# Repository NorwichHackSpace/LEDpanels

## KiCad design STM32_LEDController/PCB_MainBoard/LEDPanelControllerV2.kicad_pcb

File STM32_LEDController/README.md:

# STM32 LED Panel Controller
This controller is centered around an STM32L031C6T which can control up to 8 panels using its GPIOB output register to set 16 data lines at once, currently the code only uses 4 of the panel outputs. The output is buffered through some 74LVC2G17GW Schmitt triggers which can output at 3.3V or 5V. The main board also includes space for an optional RFM69W 433MHz module.

The main board is powered by an ATX 24-pin connector, the STM32 chip is powered by the 5V standby line (dropped to 3.3V by an LDO) whist the output buffers are powered by either the 3.3V line or the main 5V line. The STM32 controls the PSU power pin and can turn the rest of the PSU on or off whilst being powered by the standby line.

The remaining GPIO pins are broken out onto a pin header, along with GND, 3.3V (standby), and the reset pin. A HAT has been included that can provide up to 8 button inputs, assuming the 433MHz module is not present. The buttons should just connect the signal line directly to ground when pressed.

The code was compiled using STM32CubeIDE and can be uploaded by using a cheap ST-Link V2 programmer from ebay.

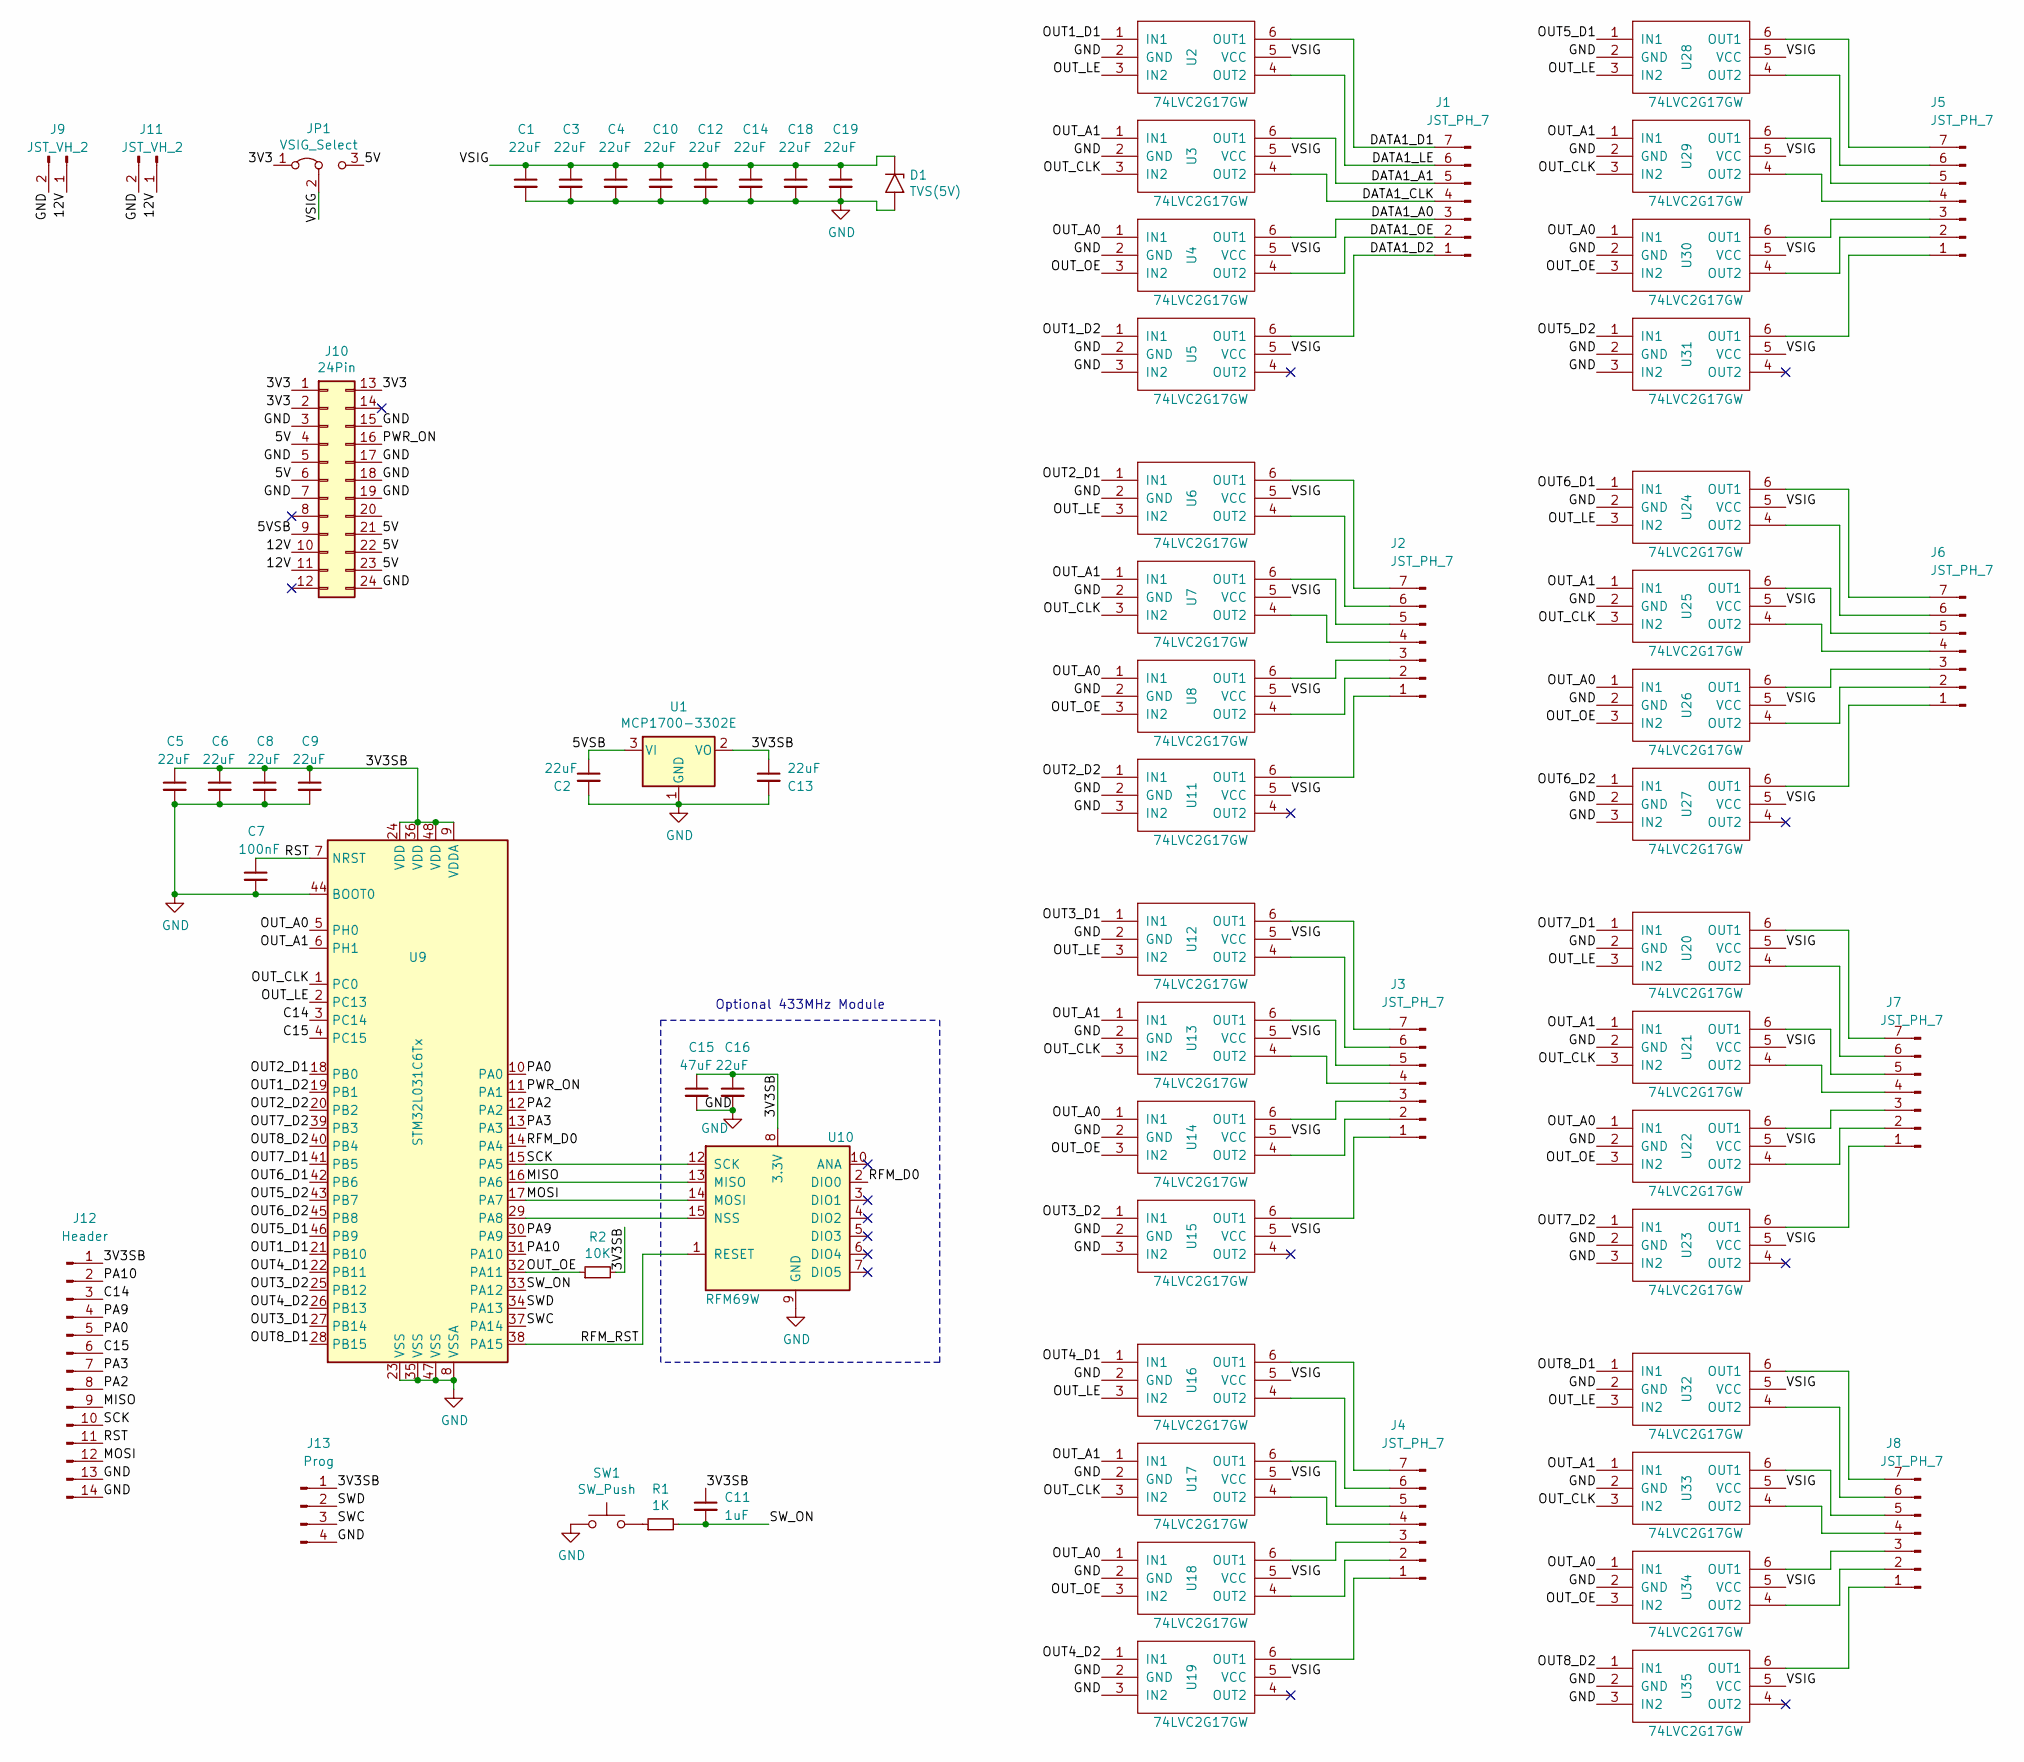
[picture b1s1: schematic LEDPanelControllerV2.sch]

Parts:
C1, C2, C3, C4, C5, C6, C8, C9, C10, C12, C13, C14, C16, C18, C19: 22uF; R_0603_HandSoldering2
C7: 100nF; R_0603_HandSoldering2
C11: 1uF; R_0603_HandSoldering2
C15: 47uF; R_1206_HandSoldering
D1: TVS(5V); DO_214AC
J1, J2, J3, J4, J5, J6, J7, J8: JST_PH_7; JST_PH_S7B-PH-SM4-TB_07x2.00mm_Angled
J9, J11: JST_VH_2; JST_VH_B2P-VH-B_2x3.96mm_Vertical
J10: 24Pin; Molex_MiniFit-JR-5569-24A2_2x12x4.20mm_Angled
J12: Header; Pin_Header_Straight_2x07_Pitch2.54mm
J13: Prog; Pin_Header_Straight_2x02_Pitch2.54mm
JP1: VSIG_Select; Pin_Header_Straight_1x03_Pitch2.54mm
R1: 1K; R_0603_HandSoldering2
R2: 10K; R_0603_HandSoldering2
SW1: SW_Push; SW_SPST_EVQQ2
U1: MCP1700-3302E; SOT-23
U2, U3, U4, U5, U6, U7, U8, U11, U12, U13, U14, U15, U16, U17, U18, U19, U20, U21, U22, U23, U24, U25, U26, U27, U28, U29, U30, U31, U32, U33, U34, U35: 74LVC2G17GW; SOT-363_SC-70-6
U9: STM32L031C6Tx; LQFP-48_7x7mm_Pitch0.5mm
U10: RFM69W; RFM69

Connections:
/3V3: J10.1, J10.2, J10.13, JP1.1 (A)
/3V3SB: C5.1, C6.1, C8.1, C9.1, C11.1, C13.1, C15.1, C16.1, J12.1, J13.1, R2.2, U1.2 (VO), U9.9 (VDDA), U9.24 (VDD), U9.36 (VDD), U9.48 (VDD), U10.8 (3.3V)
/5V: J10.4, J10.6, J10.21, J10.22, J10.23, JP1.3 (B)
/5VSB: C2.1, J10.9, U1.3 (VI)
/12V: J9.1, J10.10, J10.11, J11.1
/C14: J12.3, U9.3 (PC14)
/C15: J12.6, U9.4 (PC15)
/DATA1_A0: J1.3, U4.6 (OUT1)
/DATA1_A1: J1.5, U3.6 (OUT1)
/DATA1_CLK: J1.4, U3.4 (OUT2)
/DATA1_D1: J1.7, U2.6 (OUT1)
/DATA1_D2: J1.1, U5.6 (OUT1)
/DATA1_LE: J1.6, U2.4 (OUT2)
/DATA1_OE: J1.2, U4.4 (OUT2)
/MISO: J12.9, U9.16 (PA6), U10.13 (MISO)
/MOSI: J12.12, U9.17 (PA7), U10.14 (MOSI)
/OUT1_D1: U2.1 (IN1), U9.21 (PB10)
/OUT1_D2: U5.1 (IN1), U9.19 (PB1)
/OUT2_D1: U6.1 (IN1), U9.18 (PB0)
/OUT2_D2: U9.20 (PB2), U11.1 (IN1)
/OUT3_D1: U9.27 (PB14), U12.1 (IN1)
/OUT3_D2: U9.25 (PB12), U15.1 (IN1)
/OUT4_D1: U9.22 (PB11), U16.1 (IN1)
/OUT4_D2: U9.26 (PB13), U19.1 (IN1)
/OUT5_D1: U9.46 (PB9), U28.1 (IN1)
/OUT5_D2: U9.43 (PB7), U31.1 (IN1)
/OUT6_D1: U9.42 (PB6), U24.1 (IN1)
/OUT6_D2: U9.45 (PB8), U27.1 (IN1)
/OUT7_D1: U9.41 (PB5), U20.1 (IN1)
/OUT7_D2: U9.39 (PB3), U23.1 (IN1)
/OUT8_D1: U9.28 (PB15), U32.1 (IN1)
/OUT8_D2: U9.40 (PB4), U35.1 (IN1)
/OUT_A0: U4.1 (IN1), U8.1 (IN1), U9.5 (PH0), U14.1 (IN1), U18.1 (IN1), U22.1 (IN1), U26.1 (IN1), U30.1 (IN1), U34.1 (IN1)
/OUT_A1: U3.1 (IN1), U7.1 (IN1), U9.6 (PH1), U13.1 (IN1), U17.1 (IN1), U21.1 (IN1), U25.1 (IN1), U29.1 (IN1), U33.1 (IN1)
/OUT_CLK: U3.3 (IN2), U7.3 (IN2), U9.1 (PC0), U13.3 (IN2), U17.3 (IN2), U21.3 (IN2), U25.3 (IN2), U29.3 (IN2), U33.3 (IN2)
/OUT_LE: U2.3 (IN2), U6.3 (IN2), U9.2 (PC13), U12.3 (IN2), U16.3 (IN2), U20.3 (IN2), U24.3 (IN2), U28.3 (IN2), U32.3 (IN2)
/OUT_OE: R2.1, U4.3 (IN2), U8.3 (IN2), U9.32 (PA11), U14.3 (IN2), U18.3 (IN2), U22.3 (IN2), U26.3 (IN2), U30.3 (IN2), U34.3 (IN2)
/PA0: J12.5, U9.10 (PA0)
/PA2: J12.8, U9.12 (PA2)
/PA3: J12.7, U9.13 (PA3)
/PA9: J12.4, U9.30 (PA9)
/PA10: J12.2, U9.31 (PA10)
/PWR_ON: J10.16, U9.11 (PA1)
/RFM_D0: U9.14 (PA4), U10.2 (DIO0)
/RFM_RST: U9.38 (PA15), U10.1 (RESET)
/RST: C7.1, J12.11, U9.7 (NRST)
/SCK: J12.10, U9.15 (PA5), U10.12 (SCK)
/SWC: J13.3, U9.37 (PA14)
/SWD: J13.2, U9.34 (PA13)
/SW_ON: C11.2, R1.2, U9.33 (PA12)
/VSIG: C1.1, C3.1, C4.1, C10.1, C12.1, C14.1, C18.1, C19.1, D1.1 (A1), JP1.2 (C), U2.5 (VCC), U3.5 (VCC), U4.5 (VCC), U5.5 (VCC), U6.5 (VCC), U7.5 (VCC), U8.5 (VCC), U11.5 (VCC), U12.5 (VCC), U13.5 (VCC), U14.5 (VCC), U15.5 (VCC), U16.5 (VCC), U17.5 (VCC), U18.5 (VCC), U19.5 (VCC), U20.5 (VCC), U21.5 (VCC), U22.5 (VCC), U23.5 (VCC), U24.5 (VCC), U25.5 (VCC), U26.5 (VCC), U27.5 (VCC), U28.5 (VCC), U29.5 (VCC), U30.5 (VCC), U31.5 (VCC), U32.5 (VCC), U33.5 (VCC), U34.5 (VCC), U35.5 (VCC)
GND: C1.2, C2.2, C3.2, C4.2, C5.2, C6.2, C7.2, C8.2, C9.2, C10.2, C12.2, C13.2, C14.2, C15.2, C16.2, C18.2, C19.2, D1.2 (A2), J9.2, J10.3, J10.5, J10.7, J10.15, J10.17, J10.18, J10.19, J10.24, J11.2, J12.13, J12.14, J13.4, SW1.1, U1.1 (GND), U2.2 (GND), U3.2 (GND), U4.2 (GND), U5.2 (GND), U5.3 (IN2), U6.2 (GND), U7.2 (GND), U8.2 (GND), U9.8 (VSSA), U9.23 (VSS), U9.35 (VSS), U9.44 (BOOT0), U9.47 (VSS), U10.9 (GND), U10.11 (GND), U11.2 (GND), U11.3 (IN2), U12.2 (GND), U13.2 (GND), U14.2 (GND), U15.2 (GND), U15.3 (IN2), U16.2 (GND), U17.2 (GND), U18.2 (GND), U19.2 (GND), U19.3 (IN2), U20.2 (GND), U21.2 (GND), U22.2 (GND), U23.2 (GND), U23.3 (IN2), U24.2 (GND), U25.2 (GND), U26.2 (GND), U27.2 (GND), U27.3 (IN2), U28.2 (GND), U29.2 (GND), U30.2 (GND), U31.2 (GND), U31.3 (IN2), U32.2 (GND), U33.2 (GND), U34.2 (GND), U35.2 (GND), U35.3 (IN2)
unnamed: J2.1, U11.6 (OUT1)
unnamed: J2.2, U8.4 (OUT2)
unnamed: J2.3, U8.6 (OUT1)
unnamed: J2.4, U7.4 (OUT2)
unnamed: J2.5, U7.6 (OUT1)
unnamed: J2.6, U6.4 (OUT2)
unnamed: J2.7, U6.6 (OUT1)
unnamed: J3.1, U15.6 (OUT1)
unnamed: J3.2, U14.4 (OUT2)
unnamed: J3.3, U14.6 (OUT1)
unnamed: J3.4, U13.4 (OUT2)
unnamed: J3.5, U13.6 (OUT1)
unnamed: J3.6, U12.4 (OUT2)
unnamed: J3.7, U12.6 (OUT1)
unnamed: J4.1, U19.6 (OUT1)
unnamed: J4.2, U18.4 (OUT2)
unnamed: J4.3, U18.6 (OUT1)
unnamed: J4.4, U17.4 (OUT2)
unnamed: J4.5, U17.6 (OUT1)
unnamed: J4.6, U16.4 (OUT2)
unnamed: J4.7, U16.6 (OUT1)
unnamed: J5.1, U31.6 (OUT1)
unnamed: J5.2, U30.4 (OUT2)
unnamed: J5.3, U30.6 (OUT1)
unnamed: J5.4, U29.4 (OUT2)
unnamed: J5.5, U29.6 (OUT1)
unnamed: J5.6, U28.4 (OUT2)
unnamed: J5.7, U28.6 (OUT1)
unnamed: J6.1, U27.6 (OUT1)
unnamed: J6.2, U26.4 (OUT2)
unnamed: J6.3, U26.6 (OUT1)
unnamed: J6.4, U25.4 (OUT2)
unnamed: J6.5, U25.6 (OUT1)
unnamed: J6.6, U24.4 (OUT2)
unnamed: J6.7, U24.6 (OUT1)
unnamed: J7.1, U23.6 (OUT1)
unnamed: J7.2, U22.4 (OUT2)
unnamed: J7.3, U22.6 (OUT1)
unnamed: J7.4, U21.4 (OUT2)
unnamed: J7.5, U21.6 (OUT1)
unnamed: J7.6, U20.4 (OUT2)
unnamed: J7.7, U20.6 (OUT1)
unnamed: J8.1, U35.6 (OUT1)
unnamed: J8.2, U34.4 (OUT2)
unnamed: J8.3, U34.6 (OUT1)
unnamed: J8.4, U33.4 (OUT2)
unnamed: J8.5, U33.6 (OUT1)
unnamed: J8.6, U32.4 (OUT2)
unnamed: J8.7, U32.6 (OUT1)
unnamed: R1.1, SW1.2
unnamed: U9.29 (PA8), U10.15 (NSS)

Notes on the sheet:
Optional 433MHz Module

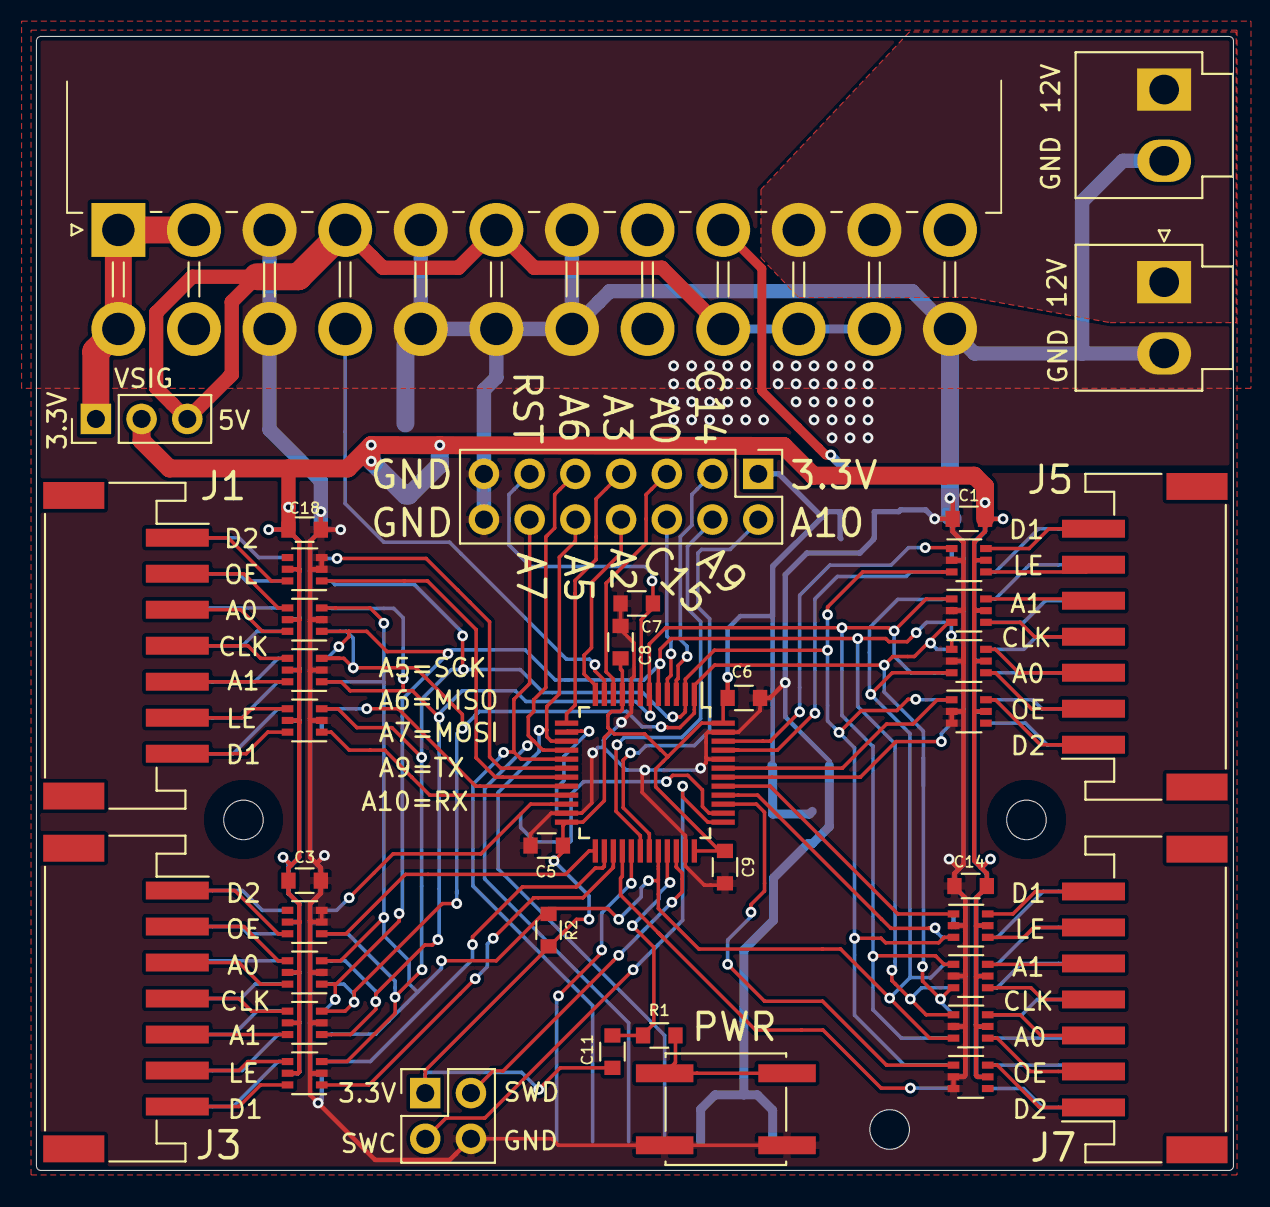
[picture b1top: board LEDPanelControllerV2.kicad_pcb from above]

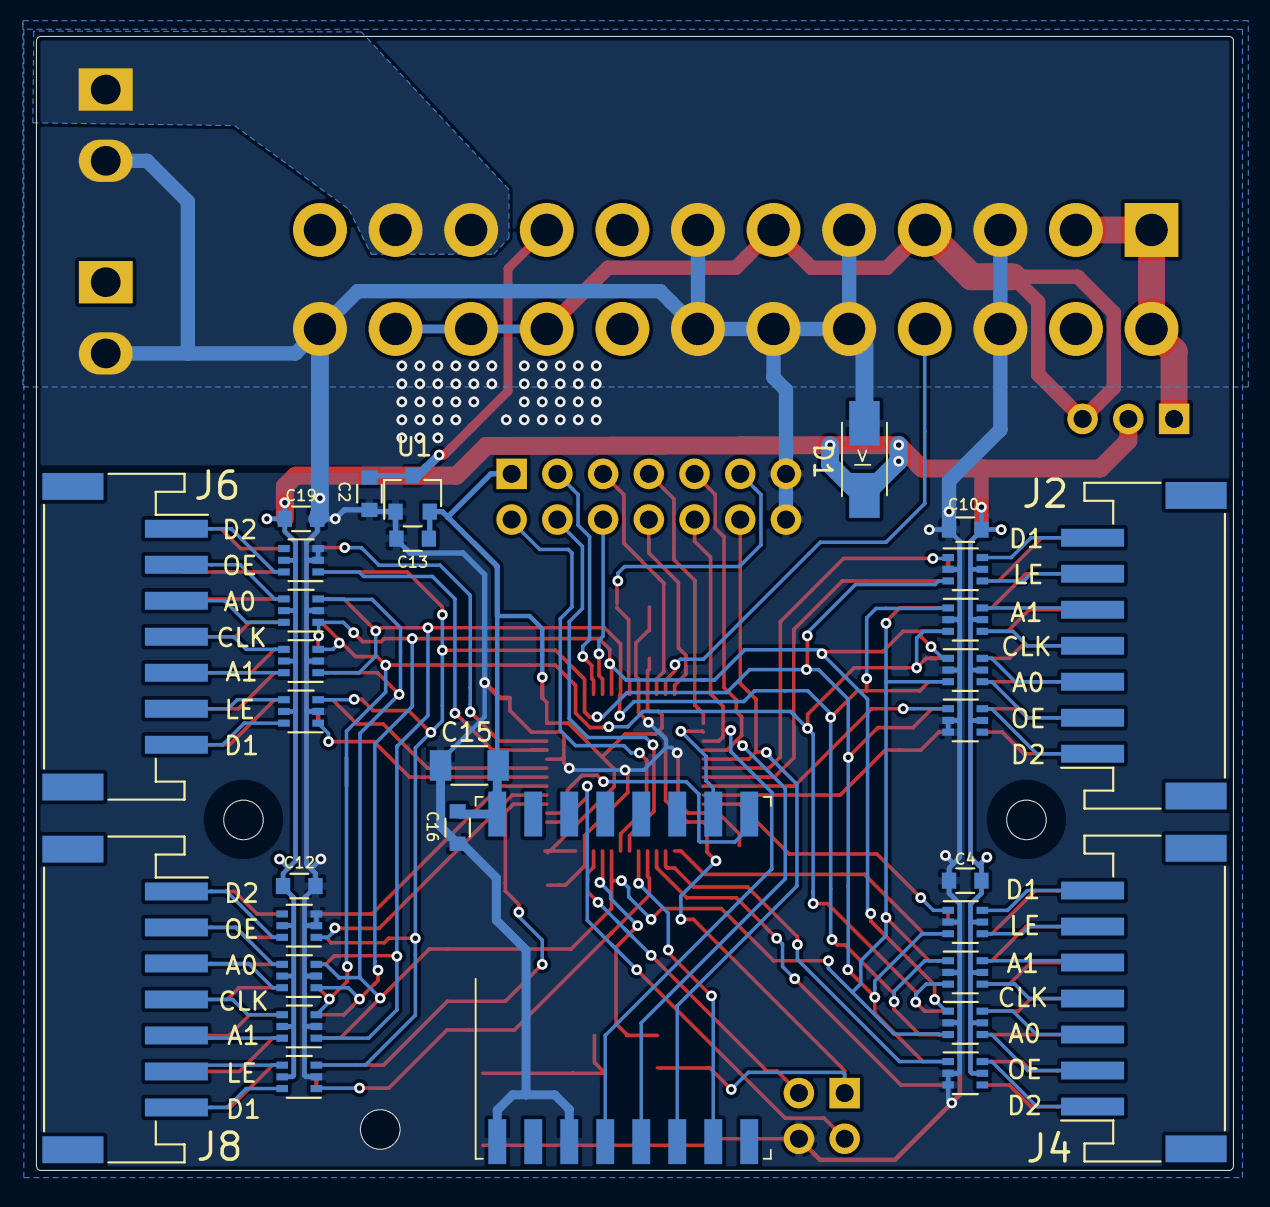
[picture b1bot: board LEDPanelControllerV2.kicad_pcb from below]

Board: 2 copper layers, 66.5 x 63.0 mm, 71 parts (31 on the bottom side), 103 nets.

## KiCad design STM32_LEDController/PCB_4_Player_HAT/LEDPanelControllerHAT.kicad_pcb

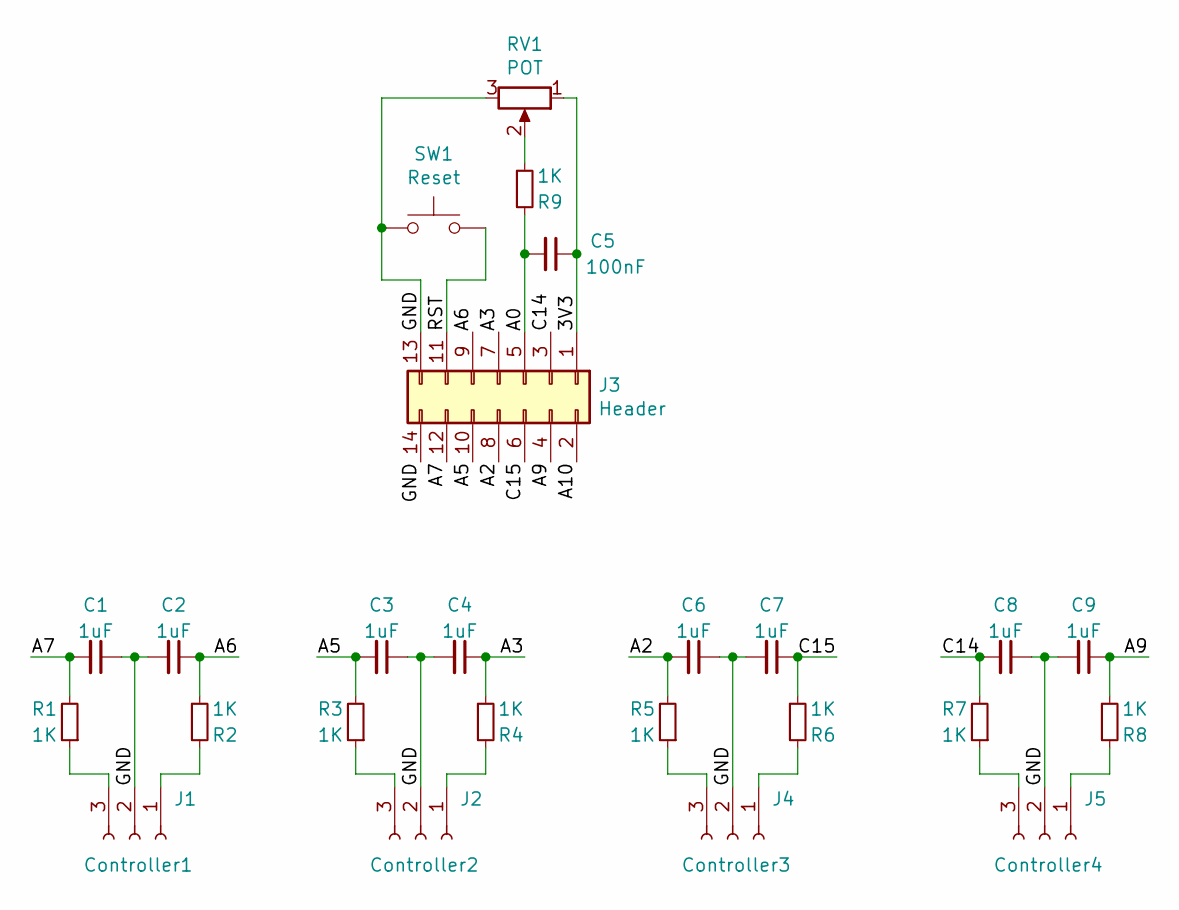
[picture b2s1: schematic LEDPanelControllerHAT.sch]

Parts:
C1, C2, C3, C4, C6, C7, C8, C9: 1uF; R_0603_HandSoldering2
C5: 100nF; R_0603_HandSoldering2
J1: Controller1; Pin_Header_Straight_1x03_Pitch1.27mm
J2: Controller2; Pin_Header_Straight_1x03_Pitch1.27mm
J3: Header; Pin_Header_Straight_2x07_Pitch2.54mm
J4: Controller3; Pin_Header_Straight_1x03_Pitch1.27mm
J5: Controller4; Pin_Header_Straight_1x03_Pitch1.27mm
R1, R2, R3, R4, R5, R6, R7, R8, R9: 1K; R_0603_HandSoldering2
RV1: POT; Potentiometer_RV09_Vertical
SW1: Reset; SW_PUSH_6mm

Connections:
/3V3: C5.1, J3.1, RV1.1
/A0: C5.2, J3.5, R9.2
/A2: C6.2, J3.8, R5.2
/A3: C4.1, J3.7, R4.1
/A5: C3.2, J3.10, R3.2
/A6: C2.1, J3.9, R2.1
/A7: C1.2, J3.12, R1.2
/A9: C9.1, J3.4, R8.1
/A10: J3.2
/C14: C8.2, J3.3, R7.2
/C15: C7.1, J3.6, R6.1
/GND: C1.1, C2.2, C3.1, C4.2, C6.1, C7.2, C8.1, C9.2, J1.2, J2.2, J3.13, J3.14, J4.2, J5.2, RV1.3, SW1.1
/RST: J3.11, SW1.2
unnamed: J1.1, R2.2
unnamed: J1.3, R1.1
unnamed: J2.1, R4.2
unnamed: J2.3, R3.1
unnamed: J4.1, R6.2
unnamed: J4.3, R5.1
unnamed: J5.1, R8.2
unnamed: J5.3, R7.1
unnamed: R9.1, RV1.2

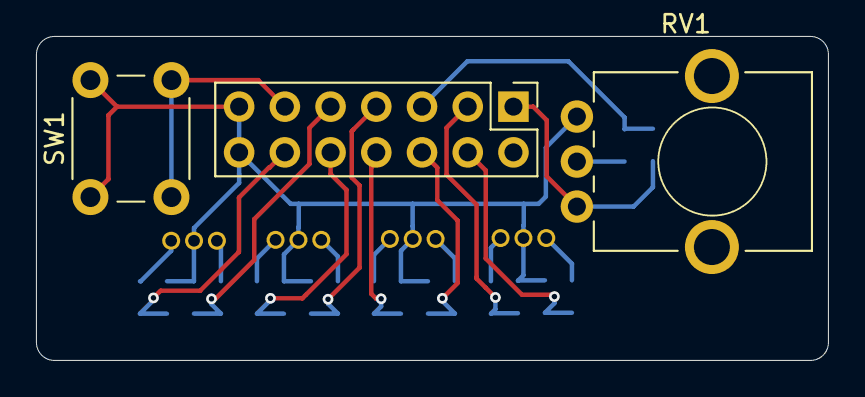
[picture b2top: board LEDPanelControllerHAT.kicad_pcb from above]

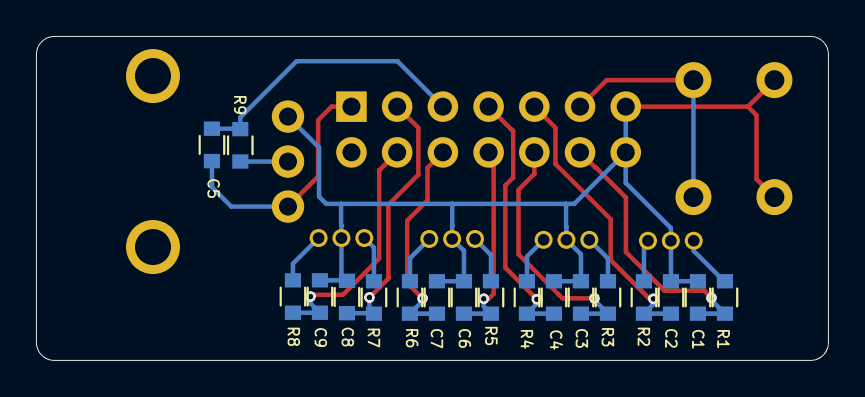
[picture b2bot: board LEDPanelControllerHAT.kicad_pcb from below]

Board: 2 copper layers, 44.0 x 18.0 mm, 25 parts (18 on the bottom side), 21 nets.

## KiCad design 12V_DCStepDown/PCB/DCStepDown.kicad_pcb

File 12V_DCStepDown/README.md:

# DCStepDown
This PCB takes 12V and steps it down to 4V (adjustable by modifying R13). Below 4V starts to change the white balance towards the blue end of the spectrum and below 3V the panels stop updating properly. Above 4V doesn't seem to change anything except use more power.

The board is built around the FAN2365 synchronous DC/DC converter which can supply up to 15A at up to 5V. With all LEDs on at 4V the board draws about 4.2A from the 12V input.

The LED data has to be clocked in as per the LED panel spec, but is passed through some 74LVC2G17 Schmitt triggers, so the data can be sent at 3.3V or 5V. The sending device must share a common ground with the board. The termination resistors can be modified based on the sender drive power and signal speed but has successfully been tested with a 60ns pulse width with 470ohm termination.

At full power the board struggles to move the heat away from the switching converter and inductor, so a 2-3mm thick piece of aluminium is recommended to be placed in the area marked "Heatsink" on the back of the board if continuous full power running is expected.

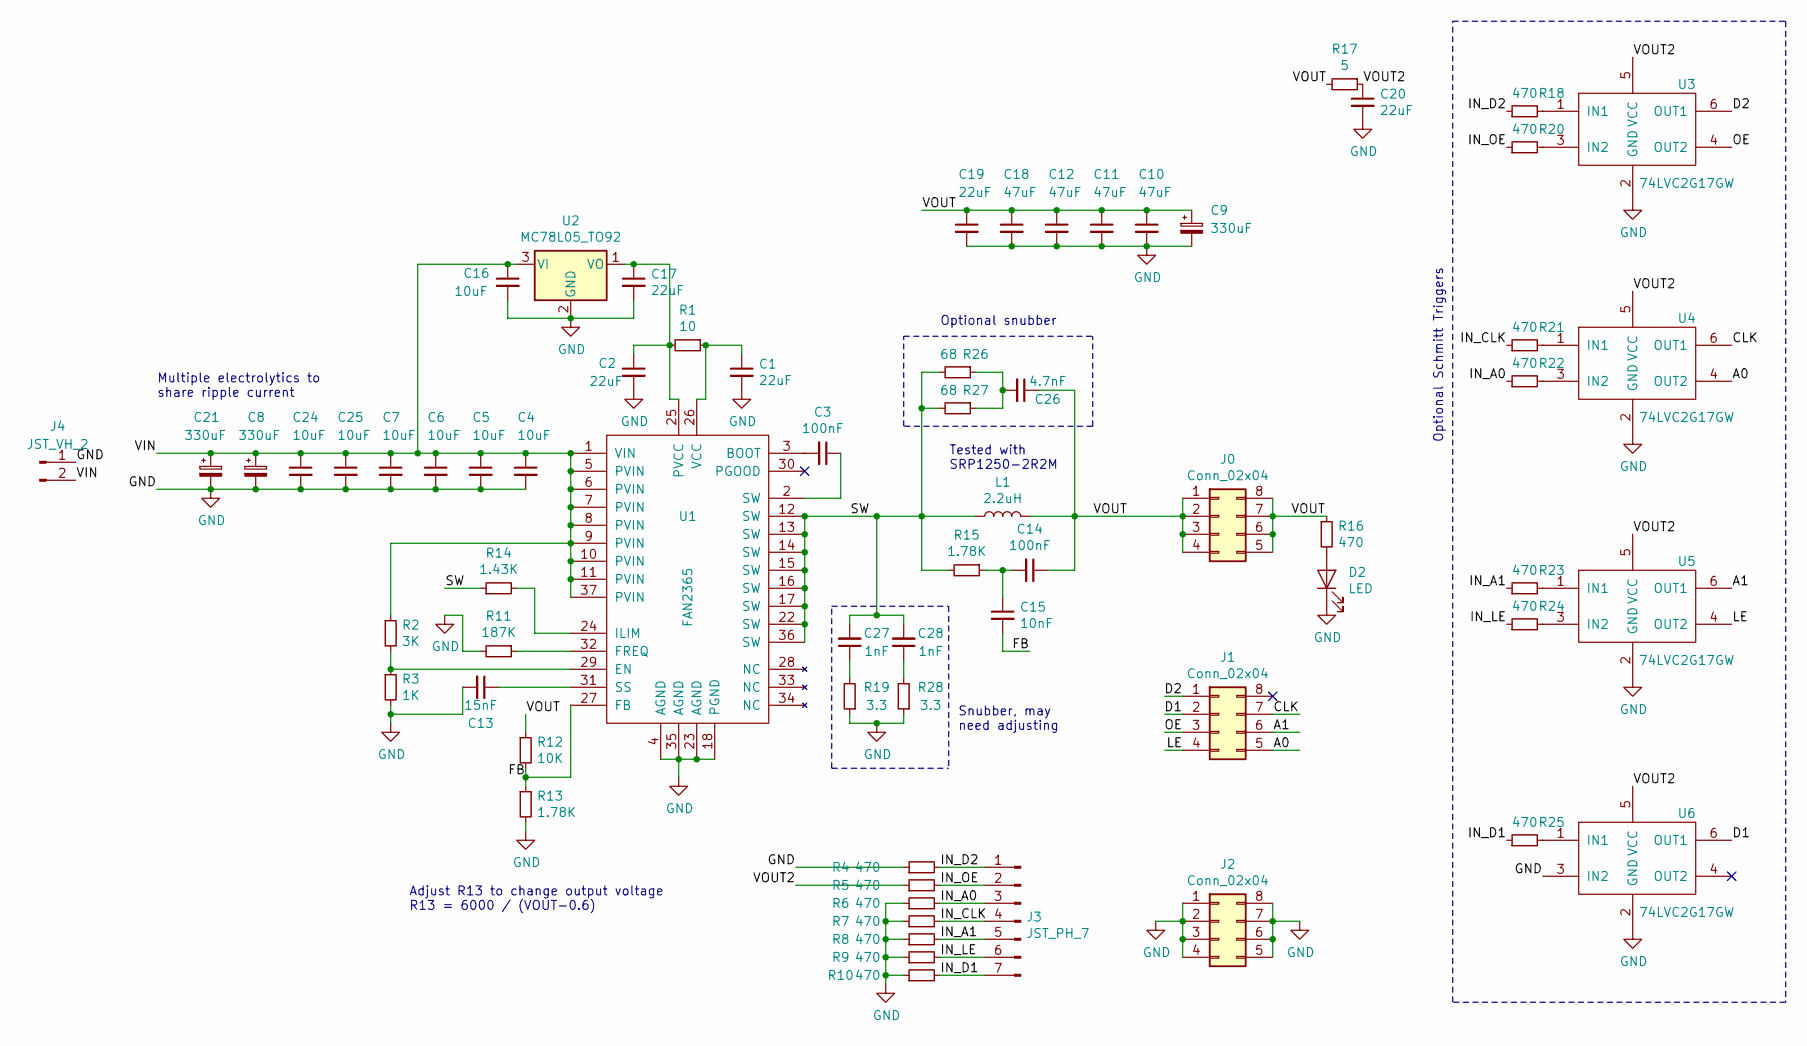
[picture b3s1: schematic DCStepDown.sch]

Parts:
C1, C2, C17, C19, C20: 22uF; R_0603_HandSoldering2
C3, C14: 100nF; R_0603_HandSoldering2
C4, C5, C6, C7, C16, C24, C25: 10uF; R_0805_HandSoldering2
C8, C9, C21: 330uF; CP_Radial_D8.0mm_P3.50mm
C10, C11, C12, C18: 47uF; R_1206_HandSoldering
C13: 15nF; R_0603_HandSoldering2
C15: 10nF; R_0603_HandSoldering2
C26: 4.7nF; R_0603_HandSoldering2
C27, C28: 1nF; R_0603_HandSoldering2
D2: LED; R_0603_HandSoldering2
J0, J1, J2: Conn_02x04; Pin_Header_Straight_2x04_Pitch2.54mm
J3: JST_PH_7; JST_PH_B7B-PH-K_07x2.00mm_Straight
J4: JST_VH_2; JST_VH_B2PS-VH_2x2x3.96mm_Horizontal
L1: 2.2uH; Inductor_SRP1250
R1: 10; R_0603_HandSoldering2
R2: 3K; R_0603_HandSoldering2
R3: 1K; R_0603_HandSoldering2
R4, R5, R6, R7, R8, R9, R10, R16, R18, R20, R21, R22, R23, R24, R25: 470; R_0603_HandSoldering2
R11: 187K; R_0603_HandSoldering2
R12: 10K; R_0603_HandSoldering2
R13, R15: 1.78K; R_0603_HandSoldering2
R14: 1.43K; R_0603_HandSoldering2
R17: 5; R_0603_HandSoldering2
R19, R28: 3.3; R_0603_HandSoldering2
R26, R27: 68; R_0603_HandSoldering2
U1: FAN2365; DC_Buck_FAN2365
U2: MC78L05_TO92; TO-92_Inline_Narrow_Oval
U3, U4, U5, U6: 74LVC2G17GW; SOT-363

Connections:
/A0: J1.5, U4.4 (OUT2)
/A1: J1.6, U5.6 (OUT1)
/CLK: J1.7, U4.6 (OUT1)
/D1: J1.2, U6.6 (OUT1)
/D2: J1.1, U3.6 (OUT1)
/FB: C15.2, R12.2, R13.1, U1.27 (FB)
/IN_A0: J3.3, R6.2, R22.1
/IN_A1: J3.5, R8.2, R23.1
/IN_CLK: J3.4, R7.2, R21.1
/IN_D1: J3.7, R10.2, R25.1
/IN_D2: J3.1, R4.2, R18.1
/IN_LE: J3.6, R9.2, R24.1
/IN_OE: J3.2, R5.2, R20.1
/LE: J1.4, U5.4 (OUT2)
/OE: J1.3, U3.4 (OUT2)
/SW: C27.2, C28.2, L1.1, R14.1, R15.2, R26.2, R27.2, U1.12 (SW), U1.13 (SW), U1.14 (SW), U1.15 (SW), U1.16 (SW), U1.17 (SW), U1.22 (SW), U1.36 (SW)
/VIN: C4.1, C5.1, C6.1, C7.1, C8.1, C16.1, C21.1, C24.1, C25.1, J4.2, R2.1, U1.1 (VIN), U1.5 (PVIN), U1.6 (PVIN), U1.7 (PVIN), U1.8 (PVIN), U1.9 (PVIN), U1.10 (PVIN), U1.11 (PVIN), U1.37 (PVIN), U2.3 (VI)
/VOUT: C9.1, C10.1, C11.1, C12.1, C14.1, C18.1, C19.1, C26.1, J0.1, J0.2, J0.3, J0.4, J0.5, J0.6, J0.7, J0.8, L1.2, R12.1, R16.1, R17.2
/VOUT2: C20.1, R5.1, R17.1, U3.5 (VCC), U4.5 (VCC), U5.5 (VCC), U6.5 (VCC)
GND: C1.2, C2.2, C4.2, C5.2, C6.2, C7.2, C8.2, C9.2, C10.2, C11.2, C12.2, C13.2, C16.2, C17.2, C18.2, C19.2, C20.2, C21.2, C24.2, C25.2, D2.1 (K), J2.1, J2.2, J2.3, J2.4, J2.5, J2.6, J2.7, J2.8, J4.1, R3.2, R4.1, R6.1, R7.1, R8.1, R9.1, R10.1, R11.2, R13.2, R19.1, R28.1, U1.4 (AGND), U1.18 (PGND), U1.23 (AGND), U1.35 (AGND), U2.2 (GND), U3.2 (GND), U4.2 (GND), U5.2 (GND), U6.2 (GND), U6.3 (IN2)
unnamed: C1.1, R1.1, U1.26 (VCC)
unnamed: C3.1, U1.2 (SW)
unnamed: C3.2, U1.3 (BOOT)
unnamed: C13.1, U1.31 (SS)
unnamed: C14.2, C15.1, R15.1
unnamed: C2.1, C17.1, R1.2, U1.25 (PVCC), U2.1 (VO)
unnamed: C26.2, R26.1, R27.1
unnamed: C27.1, R19.2
unnamed: C28.1, R28.2
unnamed: D2.2 (A), R16.2
unnamed: R2.2, R3.1, U1.29 (EN)
unnamed: R11.1, U1.32 (FREQ)
unnamed: R14.2, U1.24 (ILIM)
unnamed: R18.2, U3.1 (IN1)
unnamed: R20.2, U3.3 (IN2)
unnamed: R21.2, U4.1 (IN1)
unnamed: R22.2, U4.3 (IN2)
unnamed: R23.2, U5.1 (IN1)
unnamed: R24.2, U5.3 (IN2)
unnamed: R25.2, U6.1 (IN1)

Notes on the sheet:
Snubber, may need adjusting
Optional Schmitt Triggers
Multiple electrolytics to share ripple current
Tested with SRP1250-2R2M
Adjust R13 to change output voltage R13 = 6000 / (VOUT-0.6)
Optional snubber

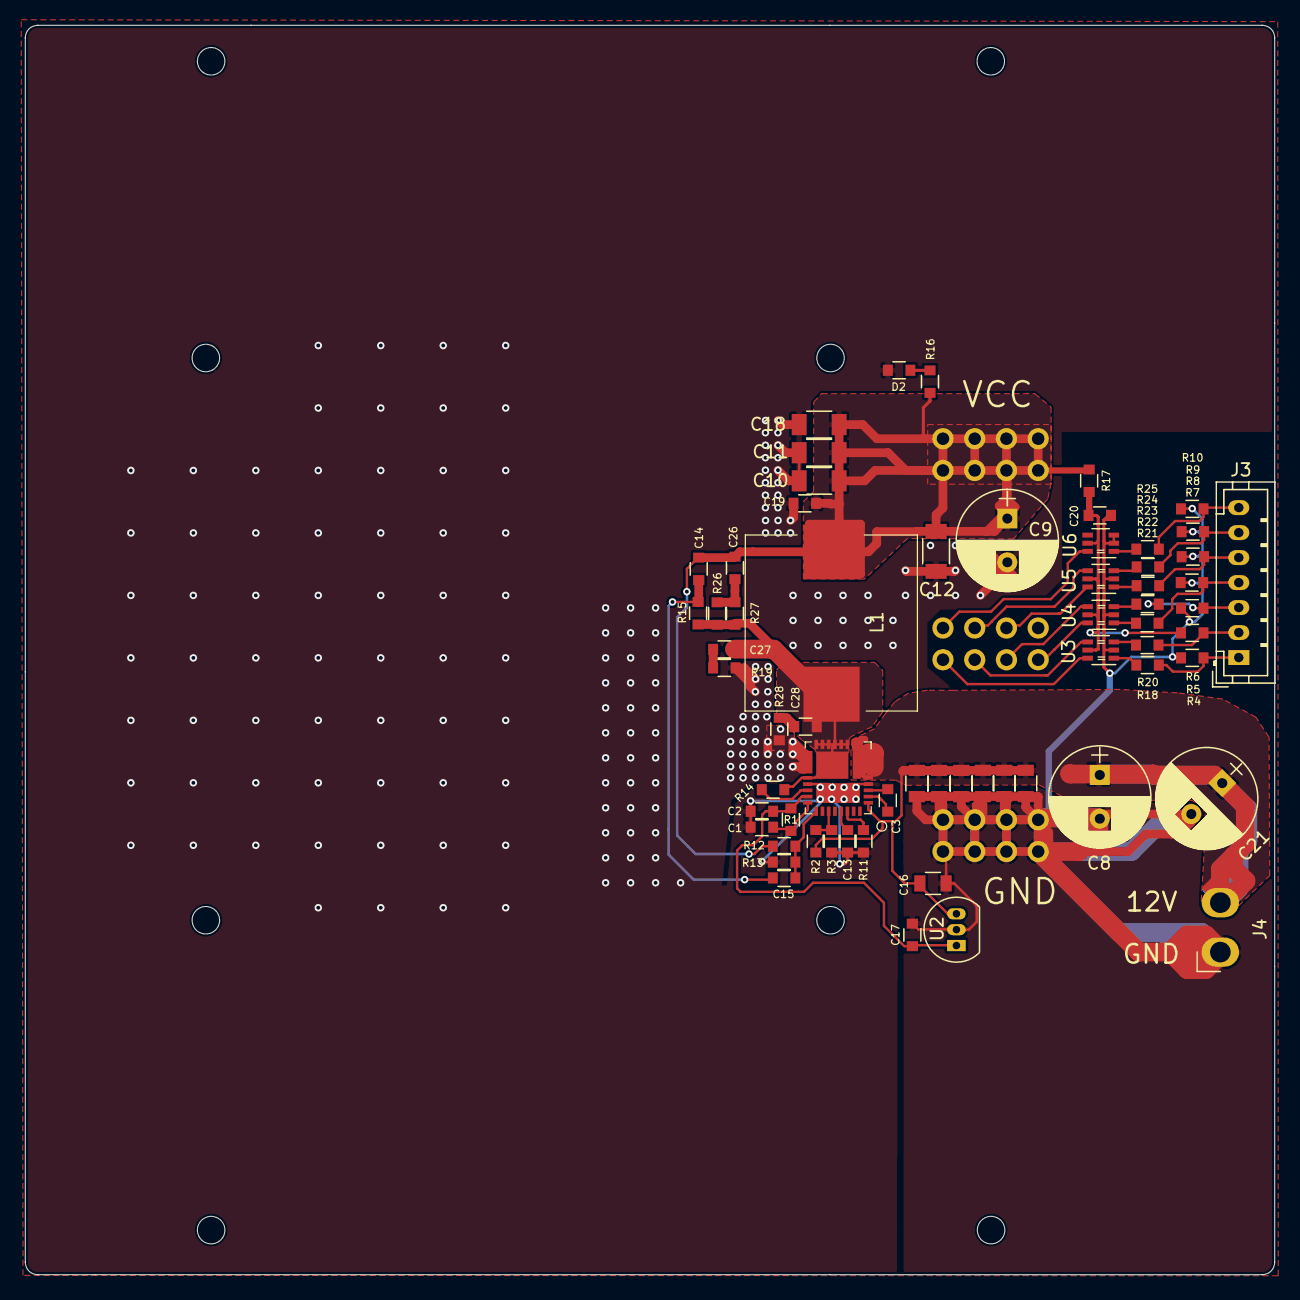
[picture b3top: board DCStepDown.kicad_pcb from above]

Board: 2 copper layers, 100.0 x 100.0 mm, 67 parts (0 on the bottom side), 40 nets.

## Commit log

2019-08-21 Fork for NHS Boards Dev
    Forking work by London Hackspace. Create folders for Norwich Hackspace's own board development work.
2019-08-21 Lolin D32 PCB V2 PCB Files
    Upload of Version 2 of the board designs for Lolin D32 dev boards.
2019-08-22 STM32L011F4P_Test Files
2019-09-05 Bare minimum test code
    Code to check the panels are working, and give a broken down example of how they work.
2019-09-08 Adafruit_GFX Example for ESP32
    Example code added that uses Adafruit GFX library for display. Note that this example is for a fixed number of four panels on BUS_D0 only, although it's quite possible to use this with less panels on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
2019-09-12 Added 12V DC Step Down Board
2019-09-12 Removed cahce file
2019-09-18 Added panel support DXF
2019-09-22 Added STM32 LED Controller
